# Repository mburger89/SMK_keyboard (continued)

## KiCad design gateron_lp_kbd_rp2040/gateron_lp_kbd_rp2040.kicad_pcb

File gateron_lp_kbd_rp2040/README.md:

# Gateron LP 5×12 Wireless Keyboard — RP2040 + RM2 radio module, Rev B

59-key (5×12, bottom row 5 + 2U + 5) hot-swap low-profile keyboard. Chip-down
RP2040 + **Raspberry Pi Radio Module 2 (RM2, RMC20452T)** for Wi-Fi 4 /
Bluetooth 5.2, per-key SK6812MINI-E RGB, Li-ion + USB-C charging, hard power
switch.

Open `gateron_lp_kbd_rp2040.kicad_pro` (file saved by KiCad 10).

## Why RM2 (Rev B change)

Rev A used a bare CYW43439 WLBGA (0.4 mm pitch) which **requires HDI
fab** (laser microvias) — several $100s for a board this size. The RM2 module
($4, FCC/CE modular certified, antenna + crystal + RF matching included) puts
the BGA on Raspberry Pi's board instead, so this board is now a **standard
4-layer** — no microvias anywhere, cheapest 4-layer tier.

## RM2 integration (exact Pico W defaults — zero firmware config)

| Signal | RP2040 GPIO | RM2 pin |
|---|---|---|
| WL_ON (Wi-Fi on + BT on) | GPIO23 | 12 + 13 |
| gSPI DATA (in / out via R14 470 Ω / nIRQ via R15 10 kΩ) | GPIO24 | 5 / 6 / 10 |
| gSPI CS | GPIO25 | 9 |
| gSPI CLK | GPIO29 | 3 |
| Vin + VDDIO | — | 16 + 14 ← +3V3 |

Matches `CYW43_DEFAULT_PIN_*` in pico-sdk: build with `PICO_CYW43_SUPPORTED=1`
and cyw43-driver + BTstack work as on a Pico W. GPIO18-22, 28 are now spare.
RM2 GPIO0/1/2 (pins 8/18/17) left unconnected.

Module placed at the top-left board edge, antenna outward, with the
datasheet-mandated **RF keepout (rule area, all 4 copper layers, no
tracks/vias/pour)** covering the on-board part of the 35.5 × 18.5 mm zone.

## PCBWay order — STANDARD 4-layer

| Setting | Value |
|---|---|
| Board size | 234.5 × 116.5 mm |
| Layers | 4, standard stackup (dielectric 1 ≈ 0.21 mm kept) |
| Thickness | 1.6 mm |
| Min track/space | 0.105 mm used locally (3.5/3.5 mil capability), mostly ≥ 0.127 |
| Vias | through 0.6/0.3 only — **no microvias, no HDI** |
| Surface finish | ENIG or HASL (no BGA anymore; ENIG still nicer for the QFN/USON) |

1. Gerbers: `export_fab.py` with KiCad's bundled Python (fills zones, plots,
   drills, zips).
2. Assembly: `pcbway_production/2026-07-17_rm2_std4layer/bom_pcbway.csv` +
   `cpl_pcbway.csv` (SMT only; SW60/61 THT hand-solder; C18 gone — no RF
   tuning needed anymore, the RM2 is pre-tuned/certified).
3. RM2 sourcing: RMC20452T, $4 RRP, reel 960 — available from RPi distributors
   (SparkFun, Pimoroni, Farnell…). Likely consignment for PCBWay.

## History of fixes (Rev A → Rev B)

- QSPI_SD1/SD2 swap at the RP2040 (would not boot) — fixed in symbol, labels,
  nets, routing.
- USB_DM was unrouted — routed.
- Y1 (12 MHz) verified vs Pico: ABM8-272-T3 with 18p (fine).
- BAT+/EN_LDO/VSYS verified connected; RGB power budget note still applies
  (firmware must cap brightness).
- Discrete CYW43439 radio section fully removed (22 parts) along with its
  routing and all 41 laser microvias; QSPI/USB_DM re-routed through-via only.
- All connectivity + clearance verified by script after every step: every net
  one island; new copper ≥ 0.105 mm to foreign nets (PCBWay 4-layer min
  0.089); holes ≥ 0.25 mm; RF keepout free of all copper.

## Remaining before ordering

- Open in KiCad, fill zones (`B`), run DRC (project rules already set:
  clearance 0.09, annular 0.05). Expect only GND-unconnected warnings that
  the pour resolves, plus courtyard/silk cosmetics.
- Confirm RM2 stock and decide consign vs. PCBWay-sourced.
- The RM2 reflows like any SMT part (peak 260 °C); PCBWay should paste the 21
  castellation lands (paste layer is defined on the footprint).

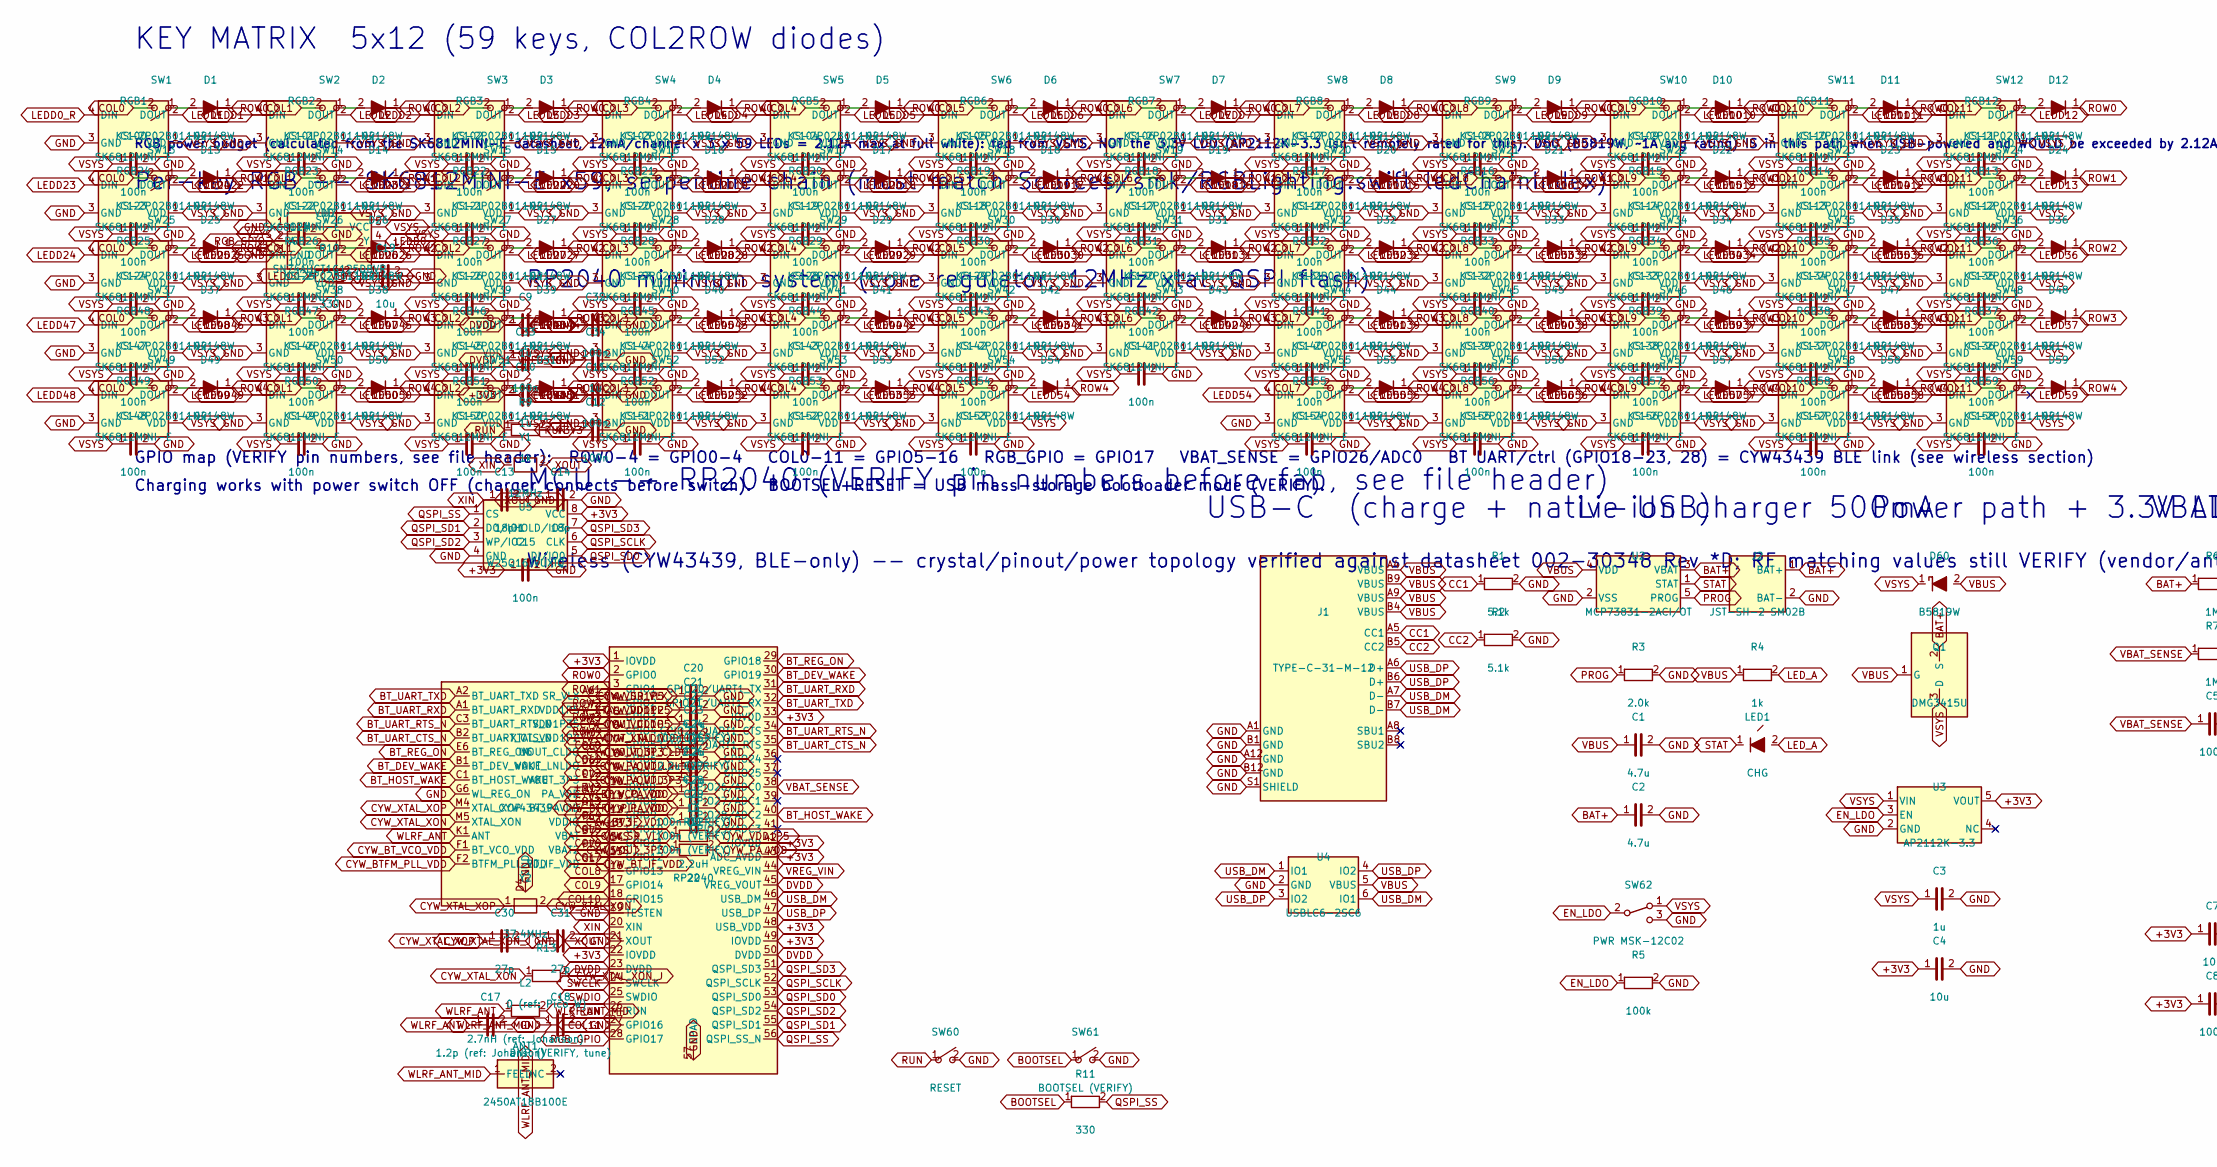
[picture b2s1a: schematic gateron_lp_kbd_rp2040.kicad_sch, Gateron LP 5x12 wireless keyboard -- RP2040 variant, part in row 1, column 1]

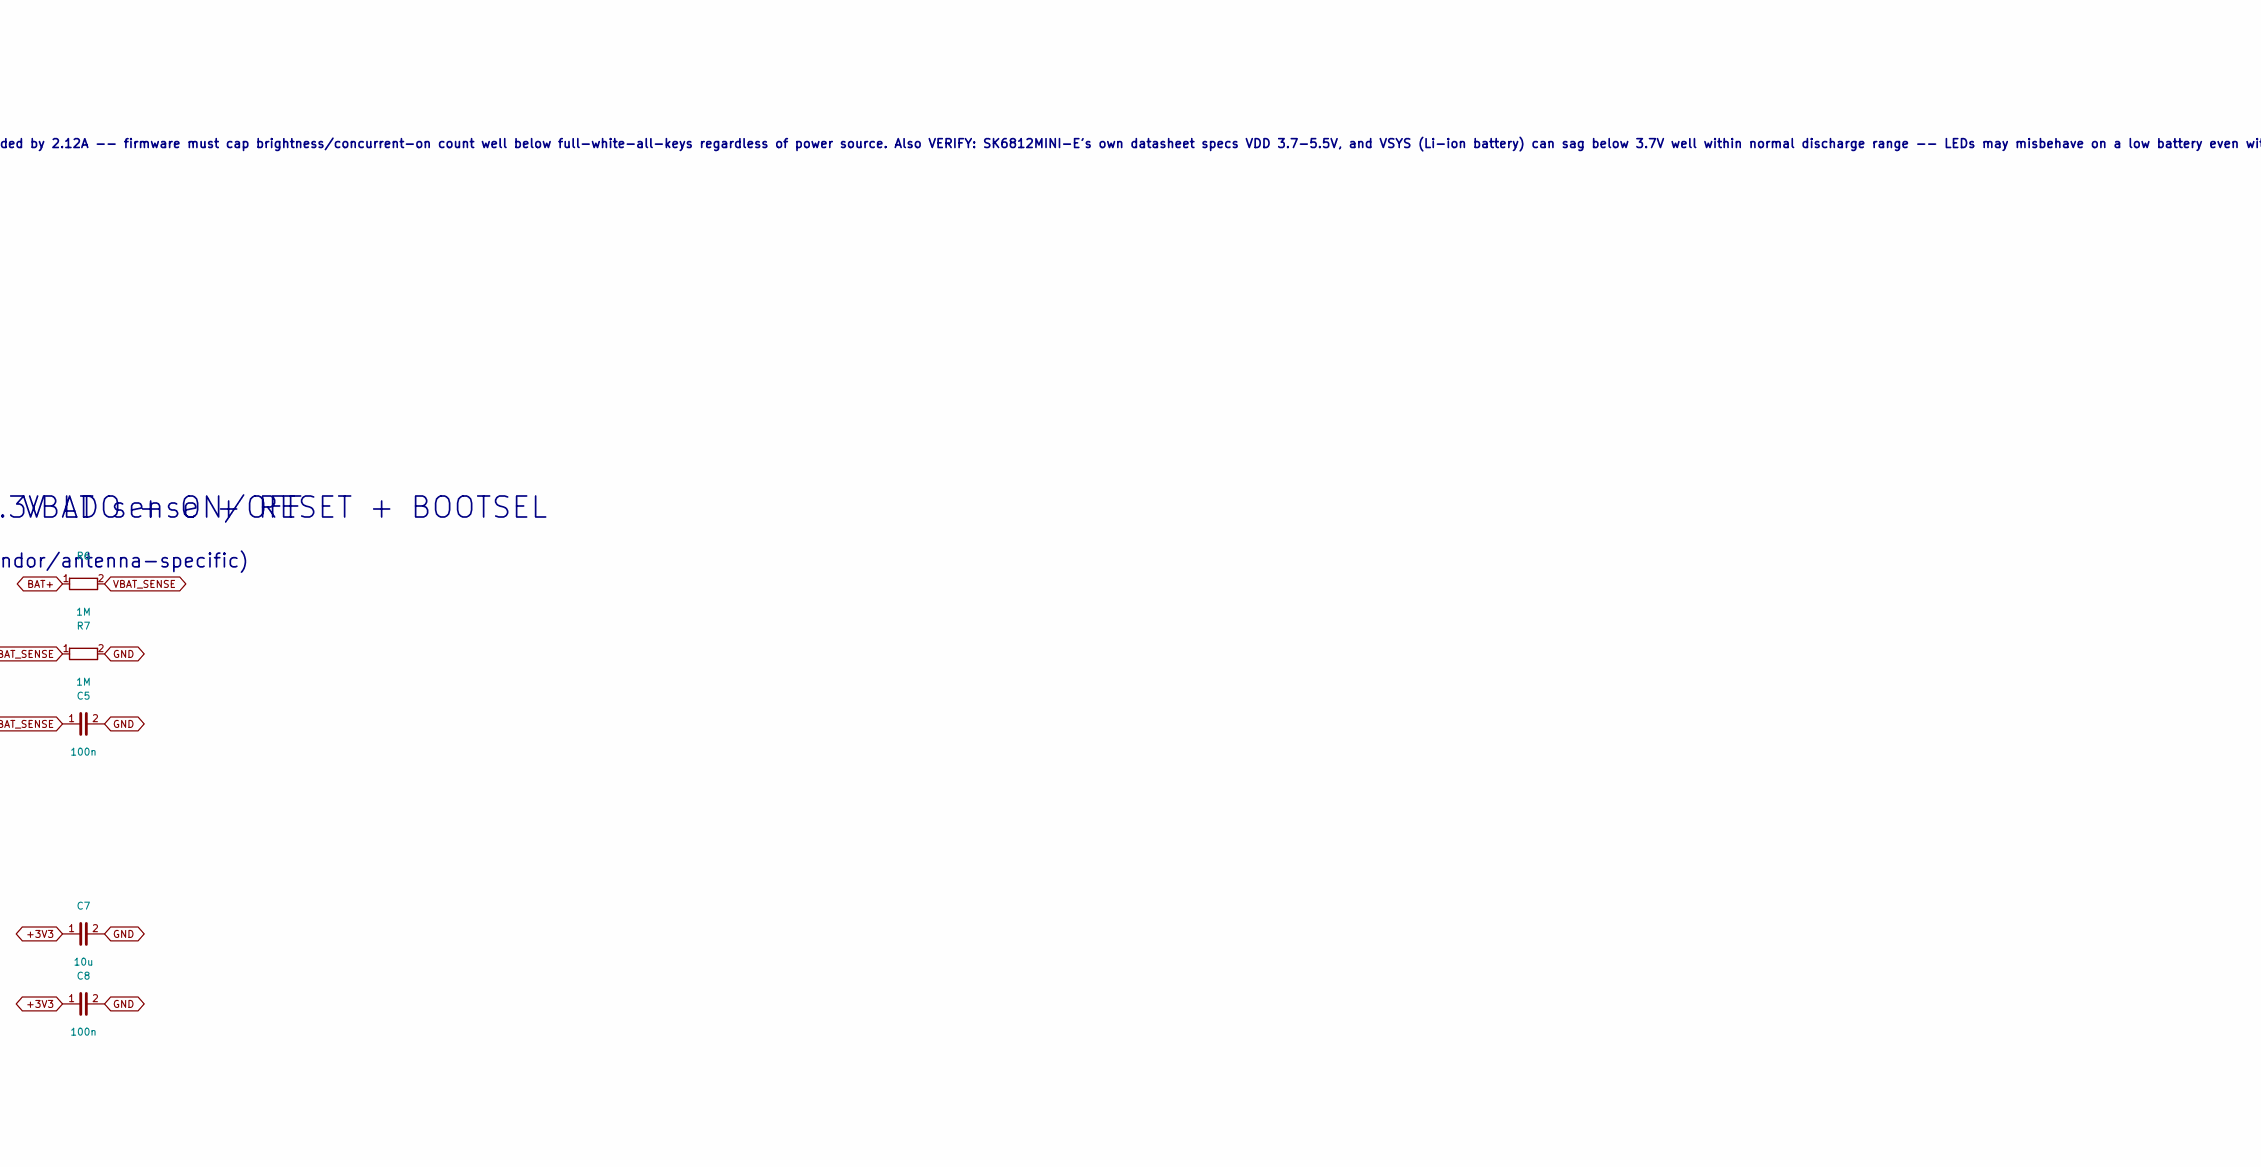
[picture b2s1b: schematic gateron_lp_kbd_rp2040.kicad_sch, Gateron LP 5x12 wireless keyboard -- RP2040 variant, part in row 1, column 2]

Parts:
ANT1: 2450AT18B100E; ANT_JOHANSON_2450AT18B100
C1, C2, C20, C24: 4.7u; RC_0603
C3, C9, C10, C25, C26, C34: 1u; RC_0603
C4, C7, C19: 10u; RC_0603
C5, C8, C11, C12, C32, C33, C100, C101, C102, C103, C104, C105, C106, C107, C108, C109, C110, C111, C112, C113, C114, C115, C116, C117, C118, C119, C120, C121, C122, C123, C124, C125, C126, C127, C128, C129, C130, C131, C132, C133, C134, C135, C136, C137, C138, C139, C140, C141, C142, C143, C144, C145, C146, C147, C148, C149, C150, C151, C152, C153, C154, C155, C156, C157, C158: 100n; RC_0603
C13, C14: 18p; RC_0603
C15: 100n; RC_0402
C17: 1.2p (ref: Johanson); RC_0402
C18: DNP (VERIFY, tune); RC_0402
C21, C27, C28, C29: 100n (VERIFY); RC_0603
C22: 2.2u; RC_0603
C23: 2.2u (VERIFY); RC_0603
C30, C31: 27p; RC_0603
D1, D2, D3, D4, D5, D6, D7, D8, D9, D10, D11, D12, D13, D14, D15, D16, D17, D18, D19, D20, D21, D22, D23, D24, D25, D26, D27, D28, D29, D30, D31, D32, D33, D34, D35, D36, D37, D38, D39, D40, D41, D42, D43, D44, D45, D46, D47, D48, D49, D50, D51, D52, D53, D54, D55, D56, D57, D58, D59: 1N4148W; D_SOD-123_Back
D60: B5819W; D_SOD-123_Back
J1: TYPE-C-31-M-12; USB_C_Receptacle_HRO_TYPE-C-31-M-12
J2: JST-SH-2 SM02B; JST_SH_SM02B_2pin_Back
L2: 2.7nH (ref: Johanson); RC_0201
L3: 2.2uH; RC_0603
LED1: CHG; LED_0603
Q1: DMG3415U; SOT-23
R1, R2: 5.1k; RC_0603
R3: 2.0k; RC_0603
R4, R9: 1k; RC_0603
R5: 100k; RC_0603
R6, R7: 1M; RC_0603
R10, R11: 330; RC_0603
R12: 22; RC_0603
R13: 0 (ref: Pico W); RC_0603
RGB1, RGB2, RGB3, RGB4, RGB5, RGB6, RGB7, RGB8, RGB9, RGB10, RGB11, RGB12, RGB13, RGB14, RGB15, RGB16, RGB17, RGB18, RGB19, RGB20, RGB21, RGB22, RGB23, RGB24, RGB25, RGB26, RGB27, RGB28, RGB29, RGB30, RGB31, RGB32, RGB33, RGB34, RGB35, RGB36, RGB37, RGB38, RGB39, RGB40, RGB41, RGB42, RGB43, RGB44, RGB45, RGB46, RGB47, RGB48, RGB49, RGB50, RGB51, RGB52, RGB53, RGB54, RGB55, RGB56, RGB57, RGB58, RGB59: SK6812MINI-E; SK6812MINI_E
SW1, SW2, SW3, SW4, SW5, SW6, SW7, SW8, SW9, SW10, SW11, SW12, SW13, SW14, SW15, SW16, SW17, SW18, SW19, SW20, SW21, SW22, SW23, SW24, SW25, SW26, SW27, SW28, SW29, SW30, SW31, SW32, SW33, SW34, SW35, SW36, SW37, SW38, SW39, SW40, SW41, SW42, SW43, SW44, SW45, SW46, SW47, SW48, SW49, SW50, SW51, SW52, SW53, SW54, SW55, SW56, SW57, SW58, SW59: KS-2P02B01-02; SW_Gateron_KS33_HS; MPN KS-2P02B01-02
SW60: RESET; SW_PUSH_6mm_THT
SW61: BOOTSEL (VERIFY); SW_PUSH_6mm_THT
SW62: PWR MSK-12C02; SW_Slide_MSK12C02
U1: RP2040; RP2040_QFN56
U2: MCP73831-2ACI/OT; SOT-23-5
U3: AP2112K-3.3; SOT-23-5
U4: USBLC6-2SC6; SOT-23-6
U5: W25Q16JVUXIQ; FLASH_USON8
U6: CYW43439; CYW43439_WLBGA63
U7: SN74AHCT1G125DBVR; SOT-23-5
Y1: 12MHz; XTAL_3225
Y2: 37.4MHz; XTAL_3225

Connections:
+3V3: C4.1, C7.1, C8.1, C10.1, C11.1, C15.1, R9.2, U1.1 (IOVDD), U1.10 (IOVDD), U1.22 (IOVDD), U1.33 (IOVDD), U1.42 (IOVDD), U1.43 (ADC_AVDD), U1.48 (USB_VDD), U1.49 (IOVDD), U3.5 (VOUT), U5.8 (VCC), U6.F6 (VDDIO)
BAT+: C2.1, J2.1 (BAT+), Q1.2 (S), R6.1, U2.3 (VBAT)
BOOTSEL: R11.1, SW61.1
BT_DEV_WAKE: U1.30 (GPIO19), U6.B1 (BT_DEV_WAKE)
BT_HOST_WAKE: U1.40 (GPIO28/ADC2), U6.C1 (BT_HOST_WAKE)
BT_REG_ON: U1.29 (GPIO18), U6.E6 (BT_REG_ON)
BT_UART_CTS_N: U1.35 (GPIO23/UART1_RTS), U6.B2 (BT_UART_CTS_N)
BT_UART_RTS_N: U1.34 (GPIO22/UART1_CTS), U6.C3 (BT_UART_RTS_N)
BT_UART_RXD: U1.31 (GPIO20/UART1_TX), U6.A1 (BT_UART_RXD)
BT_UART_TXD: U1.32 (GPIO21/UART1_RX), U6.A2 (BT_UART_TXD)
CC1: J1.A5 (CC1), R1.1
CC2: J1.B5 (CC2), R2.1
COL0: SW1.2, SW13.2, SW25.2, SW37.2, SW49.2, U1.7 (GPIO5)
COL1: SW2.2, SW14.2, SW26.2, SW38.2, SW50.2, U1.8 (GPIO6)
COL2: SW3.2, SW15.2, SW27.2, SW39.2, SW51.2, U1.9 (GPIO7)
COL3: SW4.2, SW16.2, SW28.2, SW40.2, SW52.2, U1.11 (GPIO8)
COL4: SW5.2, SW17.2, SW29.2, SW41.2, SW53.2, U1.12 (GPIO9)
COL5: SW6.2, SW18.2, SW30.2, SW42.2, SW54.2, U1.13 (GPIO10)
COL6: SW7.2, SW19.2, SW31.2, SW43.2, U1.14 (GPIO11)
COL7: SW8.2, SW20.2, SW32.2, SW44.2, SW55.2, U1.15 (GPIO12)
COL8: SW9.2, SW21.2, SW33.2, SW45.2, SW56.2, U1.16 (GPIO13)
COL9: SW10.2, SW22.2, SW34.2, SW46.2, SW57.2, U1.17 (GPIO14)
COL10: SW11.2, SW23.2, SW35.2, SW47.2, SW58.2, U1.18 (GPIO15)
COL11: SW12.2, SW24.2, SW36.2, SW48.2, SW59.2, U1.27 (GPIO16)
CYW_BTFM_PLL_VDD: C28.1, U6.F2 (BTFM_PLL_VDD)
CYW_BT_IF_VDD: C29.1, U6.G1 (BT_IF_VDD)
CYW_BT_VCO_VDD: C27.1, U6.F1 (BT_VCO_VDD)
CYW_PA_VDD: C25.1, C26.1, R12.2, U6.H1 (BT_PAVDD), U6.M1 (PA_VDD)
CYW_SR_VLX: L3.1, U6.A6 (SR_VLX)
CYW_VDD1P5: C20.1, L3.2, U6.C7 (VDD1P5), U6.M2 (VDD1P35)
CYW_VOUT_3P3: C24.1, R12.1, U6.E7 (VOUT_3P3)
CYW_VOUT_CLDO: C22.1, U6.C6 (VOUT_CLDO), U6.D3, U6.G4
CYW_VOUT_LNLDO: C23.1, U6.D6 (VOUT_LNLDO)
CYW_XTAL_VDD1P2: C21.1, U6.M3 (XTAL_VDD1P2)
CYW_XTAL_XON: R13.1, U6.M5 (XTAL_XON), Y2.2
CYW_XTAL_XON_J: C31.1, R13.2
CYW_XTAL_XOP: C30.1, U6.M4 (XTAL_XOP), Y2.1
DVDD: C9.1, C32.1, C33.1, U1.23 (DVDD), U1.45 (VREG_VOUT), U1.50 (DVDD)
EN_LDO: R5.1, SW62.2 (C), U3.3 (EN)
LEDD0: R10.1, U7.4 (Y)
LEDD0_R: R10.2, RGB1.4 (DIN)
LEDD1: RGB1.2 (DOUT), RGB2.4 (DIN)
LEDD2: RGB2.2 (DOUT), RGB3.4 (DIN)
LEDD3: RGB3.2 (DOUT), RGB4.4 (DIN)
LEDD4: RGB4.2 (DOUT), RGB5.4 (DIN)
LEDD5: RGB5.2 (DOUT), RGB6.4 (DIN)
LEDD6: RGB6.2 (DOUT), RGB7.4 (DIN)
LEDD7: RGB7.2 (DOUT), RGB8.4 (DIN)
LEDD8: RGB8.2 (DOUT), RGB9.4 (DIN)
LEDD9: RGB9.2 (DOUT), RGB10.4 (DIN)
LEDD10: RGB10.2 (DOUT), RGB11.4 (DIN)
LEDD11: RGB11.2 (DOUT), RGB12.4 (DIN)
LEDD12: RGB12.2 (DOUT), RGB13.4 (DIN)
LEDD13: RGB13.2 (DOUT), RGB14.4 (DIN)
LEDD14: RGB14.2 (DOUT), RGB15.4 (DIN)
LEDD15: RGB15.2 (DOUT), RGB16.4 (DIN)
LEDD16: RGB16.2 (DOUT), RGB17.4 (DIN)
LEDD17: RGB17.2 (DOUT), RGB18.4 (DIN)
LEDD18: RGB18.2 (DOUT), RGB19.4 (DIN)
LEDD19: RGB19.2 (DOUT), RGB20.4 (DIN)
LEDD20: RGB20.2 (DOUT), RGB21.4 (DIN)
LEDD21: RGB21.2 (DOUT), RGB22.4 (DIN)
LEDD22: RGB22.2 (DOUT), RGB23.4 (DIN)
LEDD23: RGB23.2 (DOUT), RGB24.4 (DIN)
LEDD24: RGB24.2 (DOUT), RGB25.4 (DIN)
LEDD25: RGB25.2 (DOUT), RGB26.4 (DIN)
LEDD26: RGB26.2 (DOUT), RGB27.4 (DIN)
LEDD27: RGB27.2 (DOUT), RGB28.4 (DIN)
LEDD28: RGB28.2 (DOUT), RGB29.4 (DIN)
LEDD29: RGB29.2 (DOUT), RGB30.4 (DIN)
LEDD30: RGB30.2 (DOUT), RGB31.4 (DIN)
LEDD31: RGB31.2 (DOUT), RGB32.4 (DIN)
LEDD32: RGB32.2 (DOUT), RGB33.4 (DIN)
LEDD33: RGB33.2 (DOUT), RGB34.4 (DIN)
LEDD34: RGB34.2 (DOUT), RGB35.4 (DIN)
LEDD35: RGB35.2 (DOUT), RGB36.4 (DIN)
LEDD36: RGB36.2 (DOUT), RGB37.4 (DIN)
LEDD37: RGB37.2 (DOUT), RGB38.4 (DIN)
LEDD38: RGB38.2 (DOUT), RGB39.4 (DIN)
LEDD39: RGB39.2 (DOUT), RGB40.4 (DIN)
LEDD40: RGB40.2 (DOUT), RGB41.4 (DIN)
LEDD41: RGB41.2 (DOUT), RGB42.4 (DIN)
LEDD42: RGB42.2 (DOUT), RGB43.4 (DIN)
LEDD43: RGB43.2 (DOUT), RGB44.4 (DIN)
LEDD44: RGB44.2 (DOUT), RGB45.4 (DIN)
LEDD45: RGB45.2 (DOUT), RGB46.4 (DIN)
LEDD46: RGB46.2 (DOUT), RGB47.4 (DIN)
LEDD47: RGB47.2 (DOUT), RGB48.4 (DIN)
LEDD48: RGB48.2 (DOUT), RGB49.4 (DIN)
LEDD49: RGB49.2 (DOUT), RGB50.4 (DIN)
LEDD50: RGB50.2 (DOUT), RGB51.4 (DIN)
LEDD51: RGB51.2 (DOUT), RGB52.4 (DIN)
LEDD52: RGB52.2 (DOUT), RGB53.4 (DIN)
LEDD53: RGB53.2 (DOUT), RGB54.4 (DIN)
LEDD54: RGB54.2 (DOUT), RGB55.4 (DIN)
LEDD55: RGB55.2 (DOUT), RGB56.4 (DIN)
LEDD56: RGB56.2 (DOUT), RGB57.4 (DIN)
LEDD57: RGB57.2 (DOUT), RGB58.4 (DIN)
LEDD58: RGB58.2 (DOUT), RGB59.4 (DIN)
LEDD59: RGB59.2 (DOUT)
LED_A: LED1.2, R4.2
N_R0C0: D1.2, SW1.1
N_R0C1: D2.2, SW2.1
N_R0C2: D3.2, SW3.1
N_R0C3: D4.2, SW4.1
N_R0C4: D5.2, SW5.1
N_R0C5: D6.2, SW6.1
N_R0C6: D7.2, SW7.1
N_R0C7: D8.2, SW8.1
N_R0C8: D9.2, SW9.1
N_R0C9: D10.2, SW10.1
N_R0C10: D11.2, SW11.1
N_R0C11: D12.2, SW12.1
N_R1C0: D13.2, SW13.1
N_R1C1: D14.2, SW14.1
N_R1C2: D15.2, SW15.1
N_R1C3: D16.2, SW16.1
N_R1C4: D17.2, SW17.1
N_R1C5: D18.2, SW18.1
N_R1C6: D19.2, SW19.1
N_R1C7: D20.2, SW20.1
N_R1C8: D21.2, SW21.1
N_R1C9: D22.2, SW22.1
N_R1C10: D23.2, SW23.1
N_R1C11: D24.2, SW24.1
N_R2C0: D25.2, SW25.1
N_R2C1: D26.2, SW26.1
N_R2C2: D27.2, SW27.1
N_R2C3: D28.2, SW28.1
N_R2C4: D29.2, SW29.1
N_R2C5: D30.2, SW30.1
N_R2C6: D31.2, SW31.1
N_R2C7: D32.2, SW32.1
N_R2C8: D33.2, SW33.1
N_R2C9: D34.2, SW34.1
N_R2C10: D35.2, SW35.1
N_R2C11: D36.2, SW36.1
N_R3C0: D37.2, SW37.1
N_R3C1: D38.2, SW38.1
N_R3C2: D39.2, SW39.1
N_R3C3: D40.2, SW40.1
N_R3C4: D41.2, SW41.1
N_R3C5: D42.2, SW42.1
N_R3C6: D43.2, SW43.1
N_R3C7: D44.2, SW44.1
N_R3C8: D45.2, SW45.1
N_R3C9: D46.2, SW46.1
N_R3C10: D47.2, SW47.1
N_R3C11: D48.2, SW48.1
N_R4C0: D49.2, SW49.1
N_R4C1: D50.2, SW50.1
N_R4C2: D51.2, SW51.1
N_R4C3: D52.2, SW52.1
N_R4C4: D53.2, SW53.1
N_R4C5: D54.2, SW54.1
N_R4C7: D55.2, SW55.1
N_R4C8: D56.2, SW56.1
N_R4C9: D57.2, SW57.1
N_R4C10: D58.2, SW58.1
N_R4C11: D59.2, SW59.1
PROG: R3.1, U2.5 (PROG)
QSPI_SCLK: U1.52 (QSPI_SCLK), U5.6 (CLK)
QSPI_SD0: U1.53 (QSPI_SD0), U5.5 (DI/IO0)
QSPI_SD1: U1.55 (QSPI_SD1), U5.2 (DO/IO1)
QSPI_SD2: U1.54 (QSPI_SD2), U5.3 (WP/IO2)
QSPI_SD3: U1.51 (QSPI_SD3), U5.7 (HOLD/IO3)
QSPI_SS: R11.2, U1.56 (QSPI_SS_N), U5.1 (CS)
RGB_GPIO: U1.28 (GPIO17), U7.2 (A)
ROW0: D1.1, D2.1, D3.1, D4.1, D5.1, D6.1, D7.1, D8.1, D9.1, D10.1, D11.1, D12.1, U1.2 (GPIO0)
ROW1: D13.1, D14.1, D15.1, D16.1, D17.1, D18.1, D19.1, D20.1, D21.1, D22.1, D23.1, D24.1, U1.3 (GPIO1)
ROW2: D25.1, D26.1, D27.1, D28.1, D29.1, D30.1, D31.1, D32.1, D33.1, D34.1, D35.1, D36.1, U1.4 (GPIO2)
ROW3: D37.1, D38.1, D39.1, D40.1, D41.1, D42.1, D43.1, D44.1, D45.1, D46.1, D47.1, D48.1, U1.5 (GPIO3)
ROW4: D49.1, D50.1, D51.1, D52.1, D53.1, D54.1, D55.1, D56.1, D57.1, D58.1, D59.1, U1.6 (GPIO4)
RUN: C12.1, R9.1, SW60.1, U1.26 (RUN)
STAT: LED1.1, U2.1 (STAT)
SWCLK: U1.24 (SWCLK)
SWDIO: U1.25 (SWDIO)
USB_DM: J1.A7 (D-), J1.B7 (D-), U1.46 (USB_DM), U4.1 (IO1), U4.6 (IO1)
USB_DP: J1.A6 (D+), J1.B6 (D+), U1.47 (USB_DP), U4.3 (IO2), U4.4 (IO2)
VBAT_SENSE: C5.1, R6.2, R7.1, U1.38 (GPIO26/ADC0)
VBUS: C1.1, D60.2, J1.A4 (VBUS), J1.A9 (VBUS), J1.B4 (VBUS), J1.B9 (VBUS), Q1.1 (G), R4.1, U2.4 (VDD), U4.5 (VBUS)
VREG_VIN: C34.1, U1.44 (VREG_VIN)
WLRF_ANT: C17.1, L2.1, U6.K1 (ANT)
WLRF_ANT_MID: ANT1.1 (FEED), C18.1, L2.2
XIN: C13.1, U1.20 (XIN), Y1.1
XOUT: C14.1, U1.21 (XOUT), Y1.2

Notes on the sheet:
KEY MATRIX 5x12 (59 keys, COL2ROW diodes)
MCU -- RP2040 (VERIFY pin numbers before fab, see file header)
RP2040 minimum system (core regulator, 12MHz xtal, QSPI flash)
Wireless (CYW43439, BLE-only) -- crystal/pinout/power topology verified against datasheet 002-30348 Rev *D; RF matching values still VERIFY (vendor/antenna-specific)
Per-key RGB -- SK6812MINI-E x59, serpentine chain (must match Sources/smk/RGBLighting.swift ledChainIndex)
RGB power budget (calculated from the SK6812MINI-E datasheet, 12mA/channel x 3 x 59 LEDs = 2.12A max at full white): fed from VSYS, NOT the 3.3V LDO (AP2112K-3.3 isn't remotely rated for this). D60 (B5819W, ~1A avg rating) IS in this path when USB-powered and WOULD be exceeded by 2.12A -- firmware 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
USB-C (charge + native USB)
Li-ion charger 500mA
Power path + 3.3V LDO + ON/OFF
VBAT sense + RESET + BOOTSEL
GPIO map (VERIFY pin numbers, see file header): ROW0-4 = GPIO0-4 COL0-11 = GPIO5-16 RGB_GPIO = GPIO17 VBAT_SENSE = GPIO26/ADC0 BT UART/ctrl (GPIO18-23, 28) = CYW43439 BLE link (see wireless section)
Charging works with power switch OFF (charger connects before switch). BOOTSEL+RESET = USB mass-storage bootloader mode (VERIFY).

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
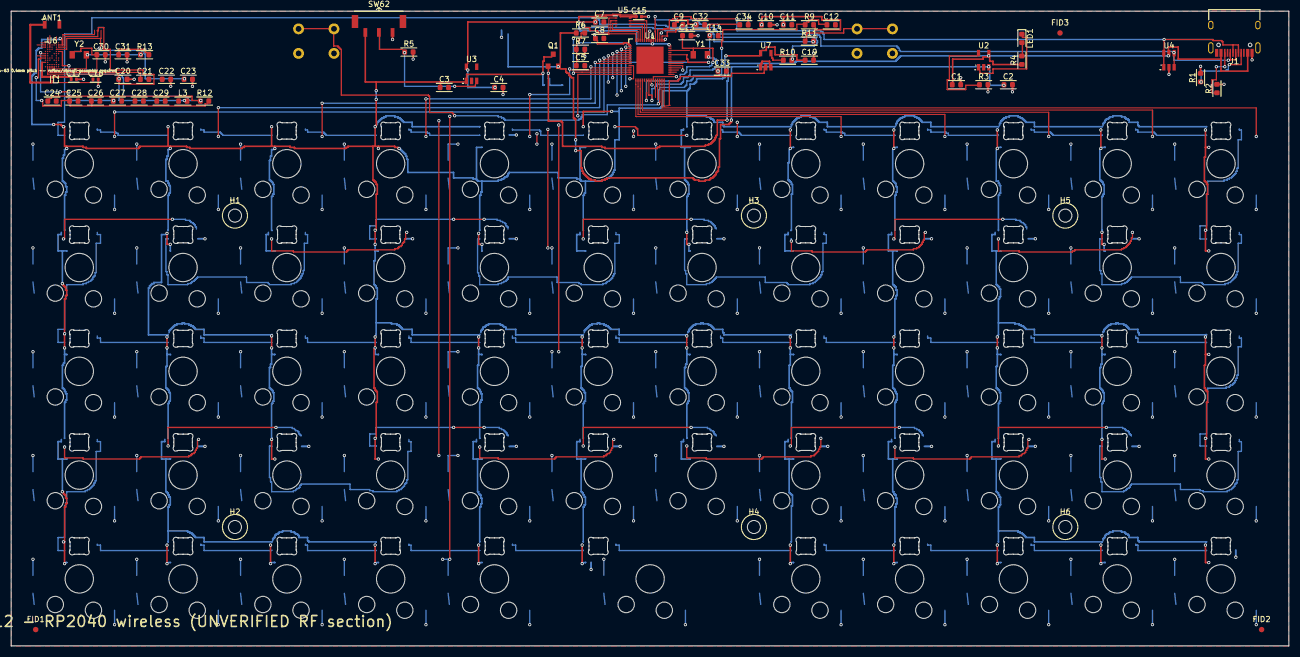
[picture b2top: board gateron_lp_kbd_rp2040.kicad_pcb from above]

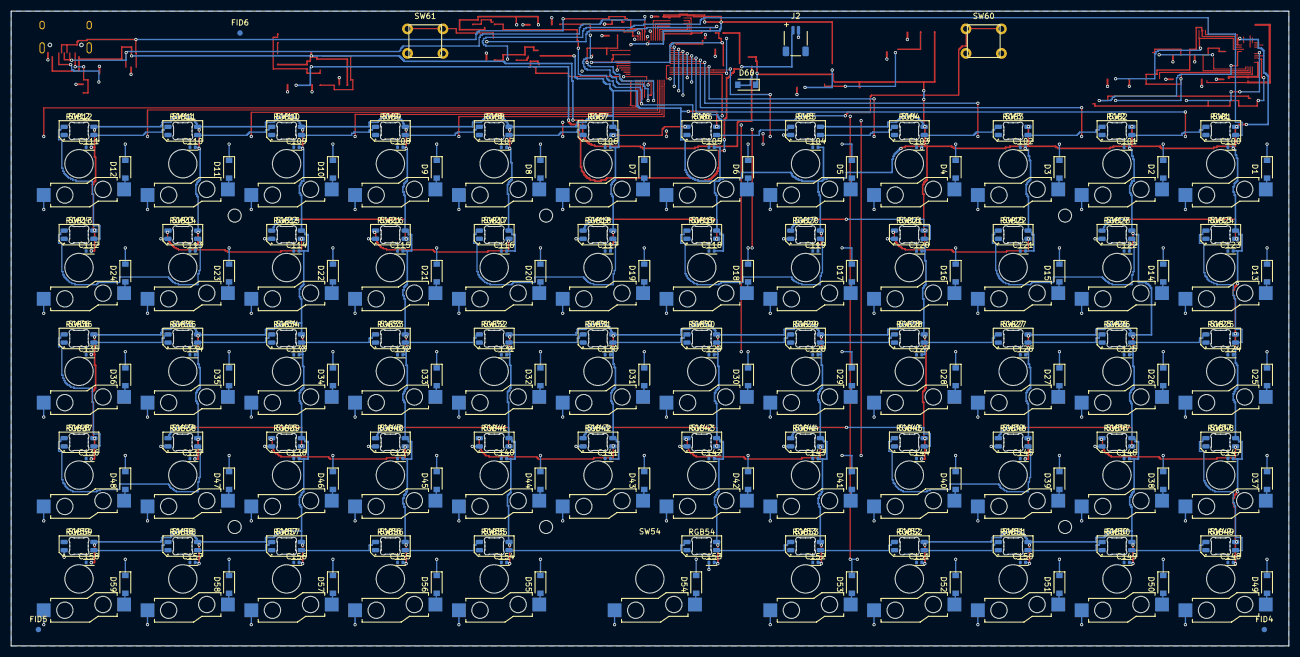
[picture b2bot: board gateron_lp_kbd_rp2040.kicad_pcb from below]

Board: 4 copper layers, 234.5 x 116.5 mm, 312 parts (243 on the bottom side), 185 nets.

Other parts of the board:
FID1, FID2, FID3, FID4, FID5, FID6: FIDUCIAL; FIDUCIAL_1MM
H1, H2, H3, H4, H5, H6: M2; MountingHole_M2

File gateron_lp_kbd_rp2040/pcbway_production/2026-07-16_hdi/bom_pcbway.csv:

Item,Designator,Qty,Manufacturer,Mfg Part #,Description / Value,Package,Type,Notes
1,ANT1,1,Johanson,2450AT18B100E,2450AT18B100E,ANT_JOHANSON_2450AT18B100,SMT,2.4GHz chip antenna
2,C1 C2 C20 C24,4,,,4.7u,RC_0603,SMT,
3,C3 C9 C10 C25 C26 C34,6,,,1u,RC_0603,SMT,
4,C4 C7 C19,3,,,10u,RC_0603,SMT,
5,C5 C8 C11 C12 C21 C27 C28 C29 C32 C33 C100 C101 C102 C103 C104 C105 C106 C107 C108 C109 C110 C111 C112 C113 C114 C115 C116 C117 C118 C119 C120 C121 C122 C123 C124 C125 C126 C127 C128 C129 C130 C131 C132 C133 C134 C135 C136 C137 C138 C139 C140 C141 C142 C143 C144 C145 C146 C147 C148 C149 C150 C151 C152 C153 C154 C155 C156 C157 C158,69,,,100n,RC_0603,SMT,
6,C13 C14,2,,,18p,RC_0603,SMT,
7,C15,1,,,100n,RC_0402,SMT,
8,C17,1,,,1.2p (ref: Johanson),RC_0402,SMT,
9,C18,1,,,DNP,RC_0402,SMT,DNP - do not populate.
10,C22 C23,2,,,2.2u,RC_0603,SMT,
11,C30 C31,2,,,6.8p,RC_0603,SMT,
12,D1 D2 D3 D4 D5 D6 D7 D8 D9 D10 D11 D12 D13 D14 D15 D16 D17 D18 D19 D20 D21 D22 D23 D24 D25 D26 D27 D28 D29 D30 D31 D32 D33 D34 D35 D36 D37 D38 D39 D40 D41 D42 D43 D44 D45 D46 D47 D48 D49 D50 D51 D52 D53 D54 D55 D56 D57 D58 D59,59,Vishay,1N4148W-E3-08,1N4148W,D_SOD-123_Back,SMT,SOD-123
13,D60,1,MDD,B5819W,B5819W,D_SOD-123_Back,SMT,Schottky 1A 40V SOD-123
14,FB1,1,Murata,BLM18AG601SN1D,BLM18AG601SN1,RC_0603,SMT,
15,J1,1,Korean Hroparts,TYPE-C-31-M-12,TYPE-C-31-M-12,USB_C_Receptacle_HRO_TYPE-C-31-M-12,SMT,USB-C 16P
16,J2,1,JST,SM02B-SRSS-TB(LF)(SN),JST-SH-2 SM02B,JST_SH_SM02B_2pin_Back,SMT,"battery, back side"
17,L2,1,,,2.7nH (ref: Johanson),RC_0201,SMT,
18,L3,1,Murata,LQM18PN2R2MGHD,2.2uH,RC_0603,SMT,2.2uH 1.05A 0603 power inductor
19,LED1,1,,,CHG,LED_0603,SMT,
20,Q1,1,Diodes Incorporated,DMG3415U-7,DMG3415U,SOT-23,SMT,
21,R1 R2,2,,,5.1k,RC_0603,SMT,
22,R3,1,,,2.0k,RC_0603,SMT,
23,R4 R9,2,,,1k,RC_0603,SMT,
24,R5,1,,,100k,RC_0603,SMT,
25,R6 R7,2,,,1M,RC_0603,SMT,
26,R10 R11,2,,,330,RC_0603,SMT,
27,R12,1,,,22,RC_0603,SMT,
28,R13,1,,,0 (ref: Pico W),RC_0603,SMT,
29,RGB1 RGB2 RGB3 RGB4 RGB5 RGB6 RGB7 RGB8 RGB9 RGB10 RGB11 RGB12 RGB13 RGB14 RGB15 RGB16 RGB17 RGB18 RGB19 RGB20 RGB21 RGB22 RGB23 RGB24 RGB25 RGB26 RGB27 RGB28 RGB29 RGB30 RGB31 RGB32 RGB33 RGB34 RGB35 RGB36 RGB37 RGB38 RGB39 RGB40 RGB41 RGB42 RGB43 RGB44 RGB45 RGB46 RGB47 RGB48 RGB49 RGB50 RGB51 RGB52 RGB53 RGB54 RGB55 RGB56 RGB57 RGB58 RGB59,59,OPSCO,SK6812MINI-E,SK6812MINI-E,SK6812MINI_E,SMT,reverse-mount RGB
30,SW1 SW2 SW3 SW4 SW5 SW6 SW7 SW8 SW9 SW10 SW11 SW12 SW13 SW14 SW15 SW16 SW17 SW18 SW19 SW20 SW21 SW22 SW23 SW24 SW25 SW26 SW27 SW28 SW29 SW30 SW31 SW32 SW33 SW34 SW35 SW36 SW37 SW38 SW39 SW40 SW41 SW42 SW43 SW44 SW45 SW46 SW47 SW48 SW49 SW50 SW51 SW52 SW53 SW54 SW55 SW56 SW57 SW58 SW59,59,Gateron,KS-2P02B01-02,KS-2P02B01-02,SW_Gateron_KS33_HS,SMT,"Hot-swap socket (soldered, PCB assembly). The Gateron KS-33 switch + keycap plug in and are ordered separately -- keyboard vendors, not on DigiKey."
31,SW60,1,,,RESET,SW_PUSH_6mm_THT,THT (hand-solder),"6x6 THT tactile switch, hand-solder"
32,SW61,1,,,BOOTSEL,SW_PUSH_6mm_THT,THT (hand-solder),"6x6 THT tactile switch, hand-solder"
33,SW62,1,Shou Han,MSK-12C02,PWR MSK-12C02,SW_Slide_MSK12C02,SMT,slide switch
34,U1,1,Raspberry Pi,SC0914,RP2040,RP2040_QFN56,SMT,
35,U2,1,Microchip,MCP73831T-2ACI/OT,MCP73831-2ACI/OT,SOT-23-5,SMT,
36,U3,1,Diodes Incorporated,AP2112K-3.3TRG1,AP2112K-3.3,SOT-23-5,SMT,
37,U4,1,STMicroelectronics,USBLC6-2SC6,USBLC6-2SC6,SOT-23-6,SMT,
38,U5,1,Winbond,W25Q16JVUXIQ TR,W25Q16JVUXIQ,FLASH_USON8,SMT,
39,U6,1,Infineon,CYW43439KUBG,CYW43439,CYW43439_WLBGA63,SMT,
40,U7,1,Texas Instruments,SN74AHCT1G125DBVR,SN74AHCT1G125DBVR,SOT-23-5,SMT,
41,Y1,1,Abracon,ABM8-272-T3,12MHz,XTAL_3225,SMT,12MHz 3225 CL=10pF (RPi-recommended)
42,Y2,1,Abracon,ABM8W-37.4000MHZ-6-K2Z-T3,37.4MHz,XTAL_3225,SMT,"37.4MHz 3225 CL=6pF; load caps 6.8p sized for CL=6, Cstray~2.5p"

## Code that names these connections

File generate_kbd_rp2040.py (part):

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    converter needing an external inductor -- the real regulator (Section
    2.10, "Core Supply Regulator") is a simple linear/LDO type (VREG_VIN ->
    VREG_VOUT -> DVDD) needing only decoupling capacitors, no inductor;
    (2) the wireless UART was wired to GPIO18-21, but UART1's real
    alternate-function pins are GPIO20-23 (Table 2) -- BT_REG_ON/
    BT_DEV_WAKE (plain GPIOs) now sit on the freed-up GPIO18/19 instead.
    Also corrected: the real chip has no perimeter GND pins at all (GND is
    only the single exposed thermal pad) -- an earlier version invented
    several. QFN-56 pad pitch/size (0.4mm, 0.25x0.6mm) is still a generic
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        # RP2040 datasheet's Core Supply Regulator chapter: the on-chip
        # regulator (VREG_VIN -> VREG_VOUT -> DVDD) is a simple linear/LDO
        # type needing only 1uF caps on VREG_VIN and VREG_VOUT plus 100nF on
        # each DVDD pin -- NO external inductor (an earlier version of this
        # file wrongly modeled it as a buck regulator with one).
        "VREG_VIN", "DVDD", "XIN", "XOUT",
        "QSPI_SCLK", "QSPI_SS", "QSPI_SD0", "QSPI_SD1", "QSPI_SD2", "QSPI_SD3",
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        "CYW_BT_VCO_VDD", "CYW_BTFM_PLL_VDD", "CYW_BT_IF_VDD",
        "WLRF_ANT", "WLRF_ANT_MID", "CYW_XTAL_XOP", "CYW_XTAL_XON", "CYW_XTAL_XON_J",
        # RGB chain
        "RGB_GPIO", "LEDD0_R"]
ROWN = {r: len(NETS) + r for r in range(5)}
NETS += [f"ROW{r}" for r in range(5)]
COLN = {c: len(NETS) + c for c in range(12)}
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# version of this file which invented several. GPIO function ASSIGNMENTS
# (which GPIO does which job -- rows/cols/RGB/BT UART/etc.) are this
# project's own choice within that real physical pin map; UART1's real
# alternate-function pins are GPIO20-23 (datasheet Table 2), which is why
# BT_REG_ON/BT_DEV_WAKE (plain GPIOs, no alt-function needed) sit on the
# freed-up GPIO18/19 instead of GPIO20-23.
# Tuple: (pin_num, label, net_name)
RP2040_PINOUT = [
    (1, "IOVDD", "+3V3"),
    (2, "GPIO0", "ROW0"), (3, "GPIO1", "ROW1"), (4, "GPIO2", "ROW2"),
    (5, "GPIO3", "ROW3"), (6, "GPIO4", "ROW4"),
    (7, "GPIO5", "COL0"), (8, "GPIO6", "COL1"), (9, "GPIO7", "COL2"),
    (10, "IOVDD", "+3V3"),
    (11, "GPIO8", "COL3"), (12, "GPIO9", "COL4"), (13, "GPIO10", "COL5"),
    (14, "GPIO11", "COL6"), (15, "GPIO12", "COL7"), (16, "GPIO13", "COL8"),
    (17, "GPIO14", "COL9"), (18, "GPIO15", "COL10"),
    (19, "TESTEN", "GND"),      # datasheet: "Factory test mode pin. Tie to GND."
    (20, "XIN", "XIN"), (21, "XOUT", "XOUT"),
    (22, "IOVDD", "+3V3"),
    (23, "DVDD", "DVDD"),
    (24, "SWCLK", "SWCLK"), (25, "SWDIO", "SWDIO"),
    (26, "RUN", "RUN"),
    (27, "GPIO16", "COL11"), (28, "GPIO17", "RGB_GPIO"),
    # CYW43439 Bluetooth is a dedicated 4-wire UART (sec. 9.2 of its own
    # datasheet), not the WLAN SDIO/gSPI bus -- BLE-only variant.
    (29, "GPIO18", "BT_REG_ON"), (30, "GPIO19", "BT_DEV_WAKE"),
    (31, "GPIO20/UART1_TX", "BT_UART_RXD"), (32, "GPIO21/UART1_RX", "BT_UART_TXD"),
    (33, "IOVDD", "+3V3"),
    (34, "GPIO22/UART1_CTS", "BT_UART_RTS_N"), (35, "GPIO23/UART1_RTS", "BT_UART_CTS_N"),
    (36, "GPIO24", None), (37, "GPIO25", None),
    (38, "GPIO26/ADC0", "VBAT_SENSE"), (39, "GPIO27/ADC1", None),
    (40, "GPIO28/ADC2", "BT_HOST_WAKE"), (41, "GPIO29/ADC3", None),
    (42, "IOVDD", "+3V3"),
    (43, "ADC_AVDD", "+3V3"),
    (44, "VREG_VIN", "VREG_VIN"), (45, "VREG_VOUT", "DVDD"),
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    # chapter (Fig. 20 application circuit): the on-chip regulator is a
    # simple linear/LDO type (VREG_VIN -> VREG_VOUT -> DVDD), NOT a buck
    # converter -- no external inductor. VREG_VIN shares the +3V3 (IOVDD)
    # rail; VREG_VOUT and both DVDD pins are one net, each needing local
    # decoupling (1uF at VREG_VOUT, 100nF at each DVDD pin per the datasheet).
    two_pin("C9", "C_kbd", "1u", 96.52, 69.85, "DVDD", "GND", C0603)      # at VREG_VOUT
    two_pin("C32", "C_kbd", "100n", 109.22, 69.85, "DVDD", "GND", C0603)  # at DVDD pin 23
    two_pin("C33", "C_kbd", "100n", 96.52, 76.2, "DVDD", "GND", C0603)    # at DVDD pin 50
    two_pin("C34", "C_kbd", "1u", 109.22, 76.2, "VREG_VIN", "GND", C0603)
    two_pin("C10", "C_kbd", "1u", 96.52, 82.55, "+3V3", "GND", C0603)   # IOVDD bulk
    two_pin("C11", "C_kbd", "100n", 109.22, 82.55, "+3V3", "GND", C0603)  # IOVDD decoupling
    two_pin("R9", "R_kbd", "1k", 96.52, 88.9, "RUN", "+3V3", R0603)     # RUN pull-up
    two_pin("C12", "C_kbd", "100n", 109.22, 88.9, "RUN", "GND", C0603)   # RUN debounce
    parts.append(sym_inst("XTAL", "Y1", "12MHz", 96.52, 95.25, 0, ["1", "2"], "kbd:XTAL_3225"))
    labels.append(sch_glabel("XIN", 92.71, 95.25, 180))
    labels.append(sch_glabel("XOUT", 100.33, 95.25, 0))
    two_pin("C13", "C_kbd", "18p", 92.71, 101.6, "XIN", "GND", C0603)
    two_pin("C14", "C_kbd", "18p", 102.87, 101.6, "XOUT", "GND", C0603)
    parts.append(sym_inst("FLASH_QSPI", "U5", "W25Q16JVUXIQ", 96.52, 107.95, 0,
                          ["1","2","3","4","5","6","7","8"], "kbd:FLASH_USON8"))
    # y = center_y - local_pin_y (Y-flip, see U1 comment above)
    labels.append(sch_glabel("QSPI_SS", 86.36, 104.14, 180))
    labels.append(sch_glabel("QSPI_SD1", 86.36, 106.68, 180))
    labels.append(sch_glabel("QSPI_SD2", 86.36, 109.22, 180))
    labels.append(sch_glabel("GND", 86.36, 111.76, 180))
    labels.append(sch_glabel("QSPI_SD0", 106.68, 111.76, 0))
    labels.append(sch_glabel("QSPI_SCLK", 106.68, 109.22, 0))
    labels.append(sch_glabel("QSPI_SD3", 106.68, 106.68, 0))
    labels.append(sch_glabel("+3V3", 106.68, 104.14, 0))
    two_pin("C15", "C_kbd", "100n", 96.52, 114.3, "+3V3", "GND", "kbd:RC_0402")

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                           "A6","C7","M2","M3","C6","D6","E7","M1","H1","F6","B7","F7","G1","D4"],
                          "kbd:CYW43439_WLBGA63"))
    # label x = center_x -/+ 12.7 (matches pin x); y = center_y - local_pin_y (Y-flip, see U1 comment above)
    labels.append(sch_glabel("BT_UART_TXD", 83.82, 137.16, 180))
    labels.append(sch_glabel("BT_UART_RXD", 83.82, 139.7, 180))
    labels.append(sch_glabel("BT_UART_RTS_N", 83.82, 142.24, 180))
    labels.append(sch_glabel("BT_UART_CTS_N", 83.82, 144.78, 180))
    labels.append(sch_glabel("BT_REG_ON", 83.82, 147.32, 180))
    labels.append(sch_glabel("BT_DEV_WAKE", 83.82, 149.86, 180))
    labels.append(sch_glabel("BT_HOST_WAKE", 83.82, 152.4, 180))
    labels.append(sch_glabel("GND", 83.82, 154.94, 180))     # WL_REG_ON tied low: WLAN unused
    labels.append(sch_glabel("CYW_XTAL_XOP", 83.82, 157.48, 180))
    labels.append(sch_glabel("CYW_XTAL_XON", 83.82, 160.02, 180))
    labels.append(sch_glabel("WLRF_ANT", 83.82, 162.56, 180))
    labels.append(sch_glabel("CYW_BT_VCO_VDD", 83.82, 165.1, 180))
    labels.append(sch_glabel("CYW_BTFM_PLL_VDD", 83.82, 167.64, 180))
    labels.append(sch_glabel("CYW_SR_VLX", 109.22, 137.16, 0))
    labels.append(sch_glabel("CYW_VDD1P5", 109.22, 139.7, 0))
    labels.append(sch_glabel("CYW_VDD1P5", 109.22, 142.24, 0))   # WLRF_VDD_1P35, same node (Fig.3)
    labels.append(sch_glabel("CYW_XTAL_VDD1P2", 109.22, 144.78, 0))
    labels.append(sch_glabel("CYW_VOUT_CLDO", 109.22, 147.32, 0))
    labels.append(sch_glabel("CYW_VOUT_LNLDO", 109.22, 149.86, 0))
    labels.append(sch_glabel("CYW_VOUT_3P3", 109.22, 152.4, 0))
    labels.append(sch_glabel("CYW_PA_VDD", 109.22, 154.94, 0))
    labels.append(sch_glabel("CYW_PA_VDD", 109.22, 157.48, 0))   # BT_PAVDD, same node (Fig.4)
    labels.append(sch_glabel("+3V3", 109.22, 160.02, 0))         # WCC_VDDIO -- must match host I/O voltage
    labels.append(sch_glabel("VSYS", 109.22, 162.56, 0))         # SR_VDDBAT5V
    labels.append(sch_glabel("VSYS", 109.22, 165.1, 0))          # LDO_VDDBAT5V
    labels.append(sch_glabel("CYW_BT_IF_VDD", 109.22, 167.64, 0))
    labels.append(sch_glabel("GND", 96.52, 172.72, 90))

    # ---- internal-rail decoupling (values per datasheet Fig.3/Fig.4 where
    # given; VERIFY where marked -- generic decoupling default, not printed
    # in the datasheet for that specific ball) ----
    two_pin("C20", "C_kbd", "4.7u", 127.0, 137.16, "CYW_VDD1P5", "GND", C0603)
    two_pin("C21", "C_kbd", "100n (VERIFY)", 127.0, 139.7, "CYW_XTAL_VDD1P2", "GND", C0603)
    two_pin("C22", "C_kbd", "2.2u", 127.0, 142.24, "CYW_VOUT_CLDO", "GND", C0603)
    two_pin("C23", "C_kbd", "2.2u (VERIFY)", 127.0, 144.78, "CYW_VOUT_LNLDO", "GND", C0603)
    two_pin("C24", "C_kbd", "4.7u", 127.0, 147.32, "CYW_VOUT_3P3", "GND", C0603)
    two_pin("C25", "C_kbd", "1u", 127.0, 149.86, "CYW_PA_VDD", "GND", C0603)
    two_pin("C26", "C_kbd", "1u", 127.0, 152.4, "CYW_PA_VDD", "GND", C0603)
    two_pin("C27", "C_kbd", "100n (VERIFY)", 127.0, 154.94, "CYW_BT_VCO_VDD", "GND", C0603)
    two_pin("C28", "C_kbd", "100n (VERIFY)", 127.0, 157.48, "CYW_BTFM_PLL_VDD", "GND", C0603)
    two_pin("C29", "C_kbd", "100n (VERIFY)", 127.0, 160.02, "CYW_BT_IF_VDD", "GND", C0603)
    two_pin("L3", "R_kbd", "2.2uH", 127.0, 162.56, "CYW_SR_VLX", "CYW_VDD1P5", R0603)  # VERIFY: inductor symbol reuse (R_kbd shape, not a real inductor symbol)
    two_pin("R12", "R_kbd", "22", 127.0, 165.1, "CYW_VOUT_3P3", "CYW_PA_VDD", R0603)
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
